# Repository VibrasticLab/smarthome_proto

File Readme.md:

# SmartHome Module

This repository contains development files for smarthome monitoring prototyping,
which intended for student final project.

Currently doesnt support any control mechanism, only measuring.

## Multi Module Version 1

### Sensors Options
- Temperature/Humidity Sensors (I2C)
    + HTU21D: [Tokped](https://www.tokopedia.com/akhishop/htu21d-temperature-and-humidity-sensor-module)
    + SHT20: [Tokped](https://www.tokopedia.com/akhishop/sht20-digital-temperature-and-humidity-sensor-module-i2c-communication)
    + SHT31-D: [Tokped](https://www.tokopedia.com/akhishop/sht31-d-temperature-humidity-sensor-module)
    + GY-213V: [Tokped](https://www.tokopedia.com/cncstorebandung/gy-213v-hdc1080-high-precision-temperature-and-humidity-sensor-module)
- Light Intensity Sensors (I2C)
    + GY302/BH1750: [Tokped](https://www.tokopedia.com/akhishop/gy-302-light-intensity-bh1750-module-sensor-intensitas-cahaya)
- CO2 Air (Analog)
    + MG-811: [Tokped](https://www.tokopedia.com/khursiot/dfrobot-analog-co2-gas-sensor-for-arduino-mg-811-sensor)
- MEMS Microphone (I2S)
    + INMP441: [Tokped](https://www.tokopedia.com/aifrobotic/inmp441-omnidirectional-microphone-module-mems-i2s-interface)

### ESP32 Pinout

NodeMCU Module: [Tokped](https://www.tokopedia.com/temins/esp32-esp-32-arduino-wifi-bluetooth-iot-development-board-micro-usb)

| I/O | Func | Connect |
|:---:|:----:|:-------:|
| EN | RESET | Pull-up Button |
| 0 | FLASH | Pull-up Button |
| 1 | TX | UART0 |
| 2 | IND | LED |
| 3 | RX | UART0 |
| 13 | SPI WS | MIC |
| 14 | SPI SCK | MIC |
| 15 | BOOT-LOG | Pull-done Resistor |
| 21 | SDA | I2C Line |
| 22 | SCL | I2C Line |
| 23 | SPI DATA | MIC |
| 33 | ADC | VBAT |
| 34 | ADC | CO2 |

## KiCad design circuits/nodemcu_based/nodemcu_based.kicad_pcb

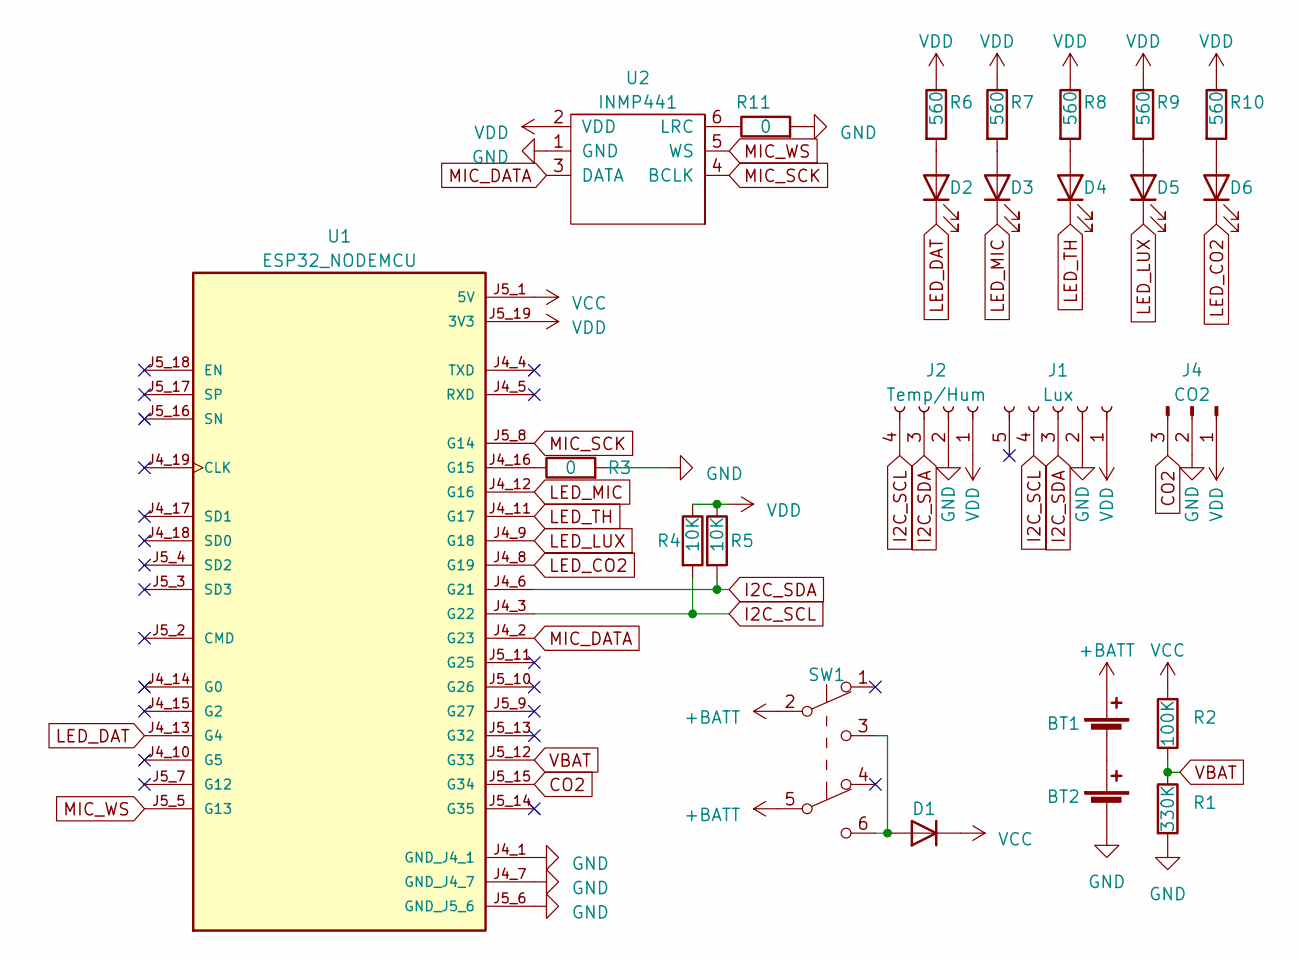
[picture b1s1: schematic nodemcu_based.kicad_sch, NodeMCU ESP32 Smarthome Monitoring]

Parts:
BT1, BT2: Battery_Cell; BatteryHolder_MPD_BH-18650-PC2
D1: D; D_DO-201_P15.24mm_Horizontal
D2, D3, D4, D5, D6: LED; LED_0805_2012Metric_Pad1.15x1.40mm_HandSolder
J1: Lux; PinSocket_1x05_P2.54mm_Vertical
J2: Temp/Hum; PinSocket_1x04_P2.54mm_Vertical
J4: CO2; PinHeader_1x03_P2.54mm_Vertical
R1: 330K; R_0805_2012Metric_Pad1.20x1.40mm_HandSolder
R2: 100K; R_0805_2012Metric_Pad1.20x1.40mm_HandSolder
R3, R11: 0; R_0805_2012Metric_Pad1.20x1.40mm_HandSolder
R4, R5: 10K; R_0805_2012Metric_Pad1.20x1.40mm_HandSolder
R6, R7, R8, R9, R10: 560; R_0805_2012Metric_Pad1.20x1.40mm_HandSolder
SW1: SW_Push_DPDT; SW_Push_2P2T_Toggle_CK_PVA2OAH5xxxxxxV2
U1: ESP32_NODEMCU; MODULE_ESP32_NODEMCU
U2: INMP441

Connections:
+BATT: BT1.1 (+), SW1.2 (B), SW1.5 (B)
CO2: J4.3, U1.J5_15 (G34)
GND: BT2.2 (-), J1.2, J2.2, J4.2, R1.2, R3.2, R11.2, U1.J4_1 (GND_J4_1), U1.J4_7 (GND_J4_7), U1.J5_6 (GND_J5_6), U2.1 (GND)
I2C_SCL: J1.4, J2.4, R4.2, U1.J4_3 (G22)
I2C_SDA: J1.3, J2.3, R5.2, U1.J4_6 (G21)
LED_CO2: D6.1 (K), U1.J4_8 (G19)
LED_DAT: D2.1 (K), U1.J4_13 (G4)
LED_LUX: D5.1 (K), U1.J4_9 (G18)
LED_MIC: D3.1 (K), U1.J4_12 (G16)
LED_TH: D4.1 (K), U1.J4_11 (G17)
MIC_DATA: U1.J4_2 (G23), U2.3 (DATA)
MIC_SCK: U1.J5_8 (G14), U2.4 (BCLK)
MIC_WS: U1.J5_5 (G13), U2.5 (WS)
unnamed: BT1.2 (-), BT2.1 (+)
unnamed: D1.2 (A), SW1.3 (C), SW1.6 (C)
unnamed: D2.2 (A), R6.2
unnamed: D3.2 (A), R7.2
unnamed: D4.2 (A), R8.2
unnamed: D5.2 (A), R9.2
unnamed: D6.2 (A), R10.2
unnamed: R3.1, U1.J4_16 (G15)
unnamed: R11.1, U2.6 (LRC)
VBAT: R1.1, R2.2, U1.J5_12 (G33)
VCC: D1.1 (K), R2.1, U1.J5_1 (5V)
VDD: J1.1, J2.1, J4.1, R4.1, R5.1, R6.1, R7.1, R8.1, R9.1, R10.1, U1.J5_19 (3V3), U2.2 (VDD)

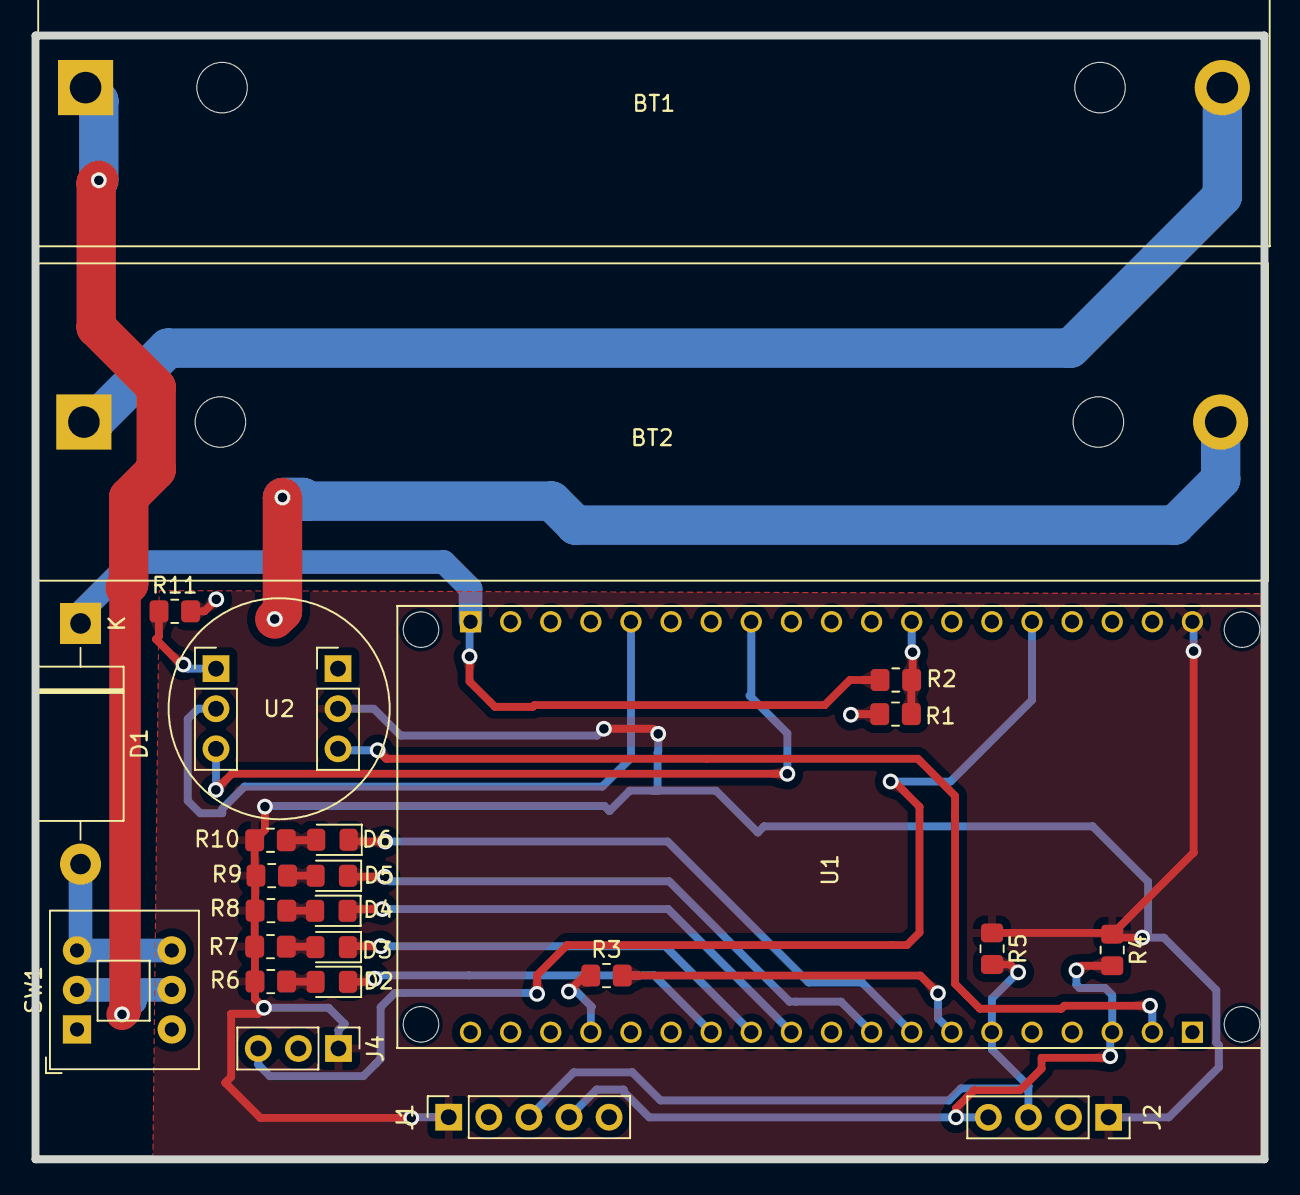
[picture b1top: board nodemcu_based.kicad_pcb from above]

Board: 2 copper layers, 77.8 x 71.2 mm, 25 parts (0 on the bottom side), 25 nets.

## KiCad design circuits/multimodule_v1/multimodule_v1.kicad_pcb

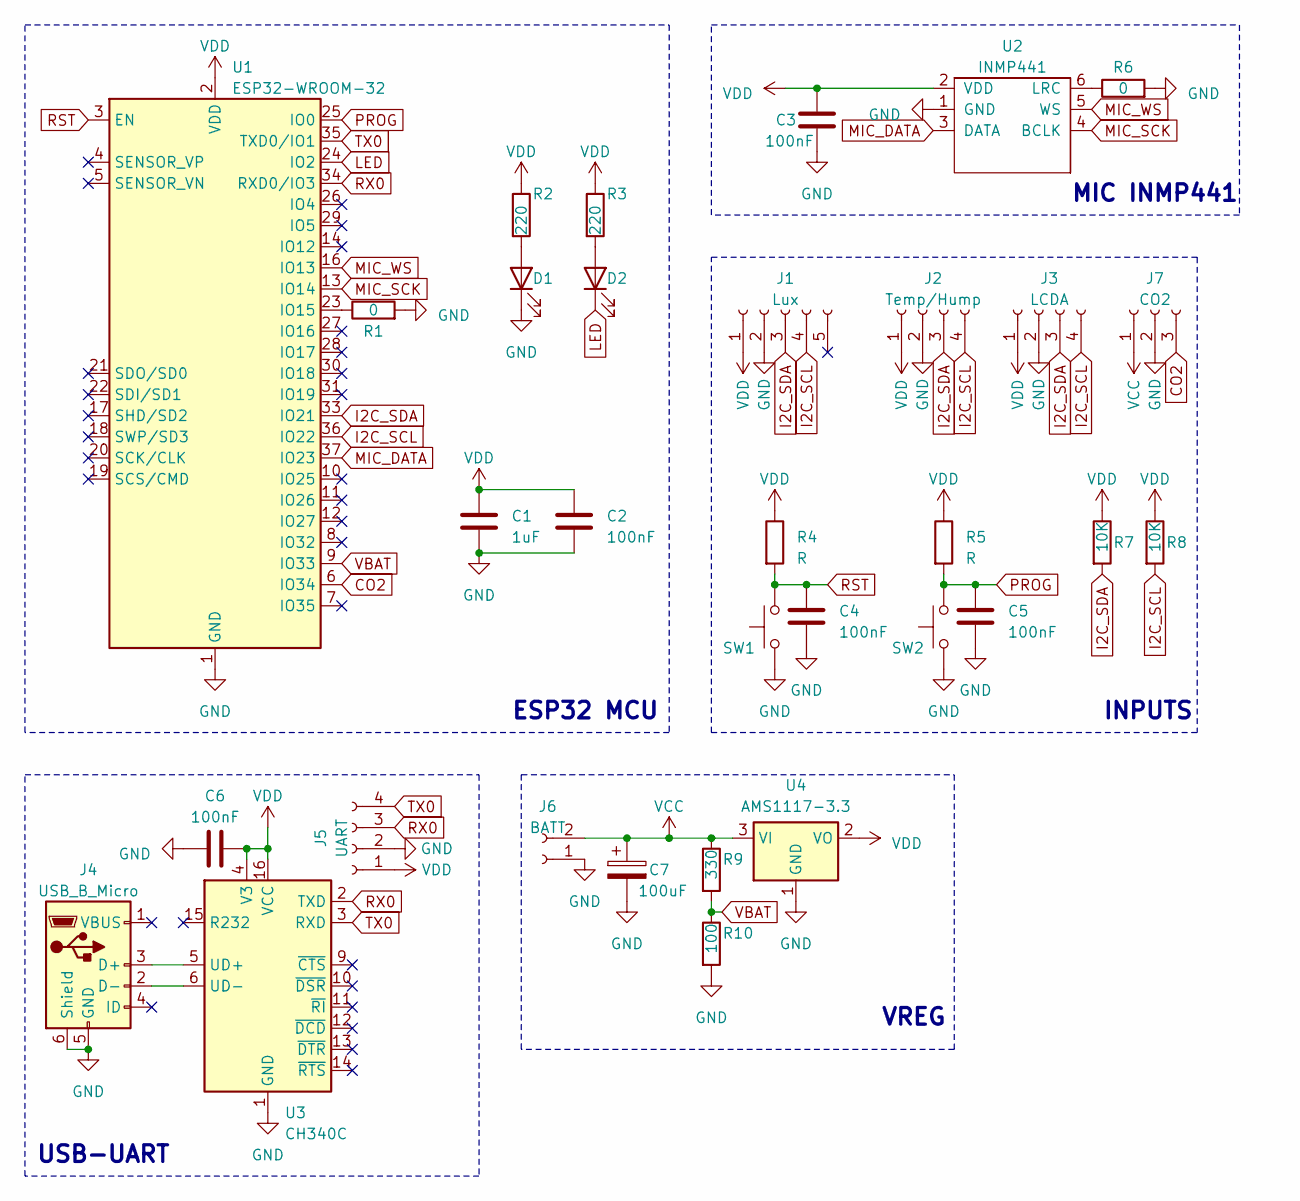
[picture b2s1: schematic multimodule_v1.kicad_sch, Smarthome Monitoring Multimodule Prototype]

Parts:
C1: 1uF; C_0805_2012Metric_Pad1.18x1.45mm_HandSolder
C2, C3, C4, C5, C6: 100nF; C_0805_2012Metric_Pad1.18x1.45mm_HandSolder
C7: 100uF; CP_Elec_4x5.8
D1, D2: LED; LED_0805_2012Metric_Pad1.15x1.40mm_HandSolder
J1: Lux; PinSocket_1x05_P2.54mm_Vertical
J2: Temp/Hump; PinSocket_1x04_P2.54mm_Vertical
J3: LCDA; PinSocket_1x04_P2.54mm_Vertical
J4: USB_B_Micro; USB_Micro-B_Wuerth_629105150521
J5: UART; PinHeader_1x04_P2.54mm_Vertical
J6: BATT; TerminalBlock_4Ucon_1x02_P3.50mm_Horizontal
J7: CO2; PinHeader_1x03_P2.54mm_Vertical
R1, R6: 0; R_0805_2012Metric_Pad1.20x1.40mm_HandSolder
R2, R3: 220; R_0805_2012Metric_Pad1.20x1.40mm_HandSolder
R4, R5: R; R_0805_2012Metric_Pad1.20x1.40mm_HandSolder
R7, R8: 10K; R_0805_2012Metric_Pad1.20x1.40mm_HandSolder
R9: 330; R_0805_2012Metric_Pad1.20x1.40mm_HandSolder
R10: 100; R_0805_2012Metric_Pad1.20x1.40mm_HandSolder
SW1, SW2: SW_Push; SW_PUSH_6mm
U1: ESP32-WROOM-32
U2: INMP441
U3: CH340C; SOIC-16_3.9x9.9mm_P1.27mm
U4: AMS1117-3.3; SOT-223-3_TabPin2

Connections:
CO2: J7.3, U1.6 (IO34)
GND: C1.2, C2.2, C3.2, C4.2, C5.2, C6.1, C7.2, D1.1 (K), J1.2, J2.2, J3.2, J4.5 (GND), J4.6 (Shield), J5.2, J6.1, J7.2, R1.2, R6.2, R10.2, SW1.1, SW2.1, U1.1 (GND), U1.15 (GND), U1.38 (GND), U1.39 (GND), U2.1 (GND), U3.1 (GND), U4.1 (GND)
I2C_SCL: J1.4, J2.4, J3.4, R8.2, U1.36 (IO22)
I2C_SDA: J1.3, J2.3, J3.3, R7.2, U1.33 (IO21)
LED: D2.1 (K), U1.24 (IO2)
MIC_DATA: U1.37 (IO23), U2.3 (DATA)
MIC_SCK: U1.13 (IO14), U2.4 (BCLK)
MIC_WS: U1.16 (IO13), U2.5 (WS)
unnamed: D1.2 (A), R2.2
unnamed: D2.2 (A), R3.2
unnamed: J4.3 (D+), U3.5 (UD+)
unnamed: J4.2 (D-), U3.6 (UD-)
unnamed: R1.1, U1.23 (IO15)
unnamed: R6.1, U2.6 (LRC)
PROG: C5.1, R5.2, SW2.2, U1.25 (IO0)
RST: C4.1, R4.2, SW1.2, U1.3 (EN)
RX0: J5.3, U1.34 (RXD0/IO3), U3.2 (TXD)
TX0: J5.4, U1.35 (TXD0/IO1), U3.3 (RXD)
VBAT: R9.2, R10.1, U1.9 (IO33)
VCC: C7.1, J6.2, J7.1, R9.1, U4.3 (VI)
VDD: C1.1, C2.1, C3.1, C6.2, J1.1, J2.1, J3.1, J5.1, R2.1, R3.1, R4.1, R5.1, R7.1, R8.1, U1.2 (VDD), U2.2 (VDD), U3.4 (V3), U3.16 (VCC), U4.2 (VO)

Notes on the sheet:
USB-UART
ESP32 MCU
VREG
INPUTS
MIC INMP441

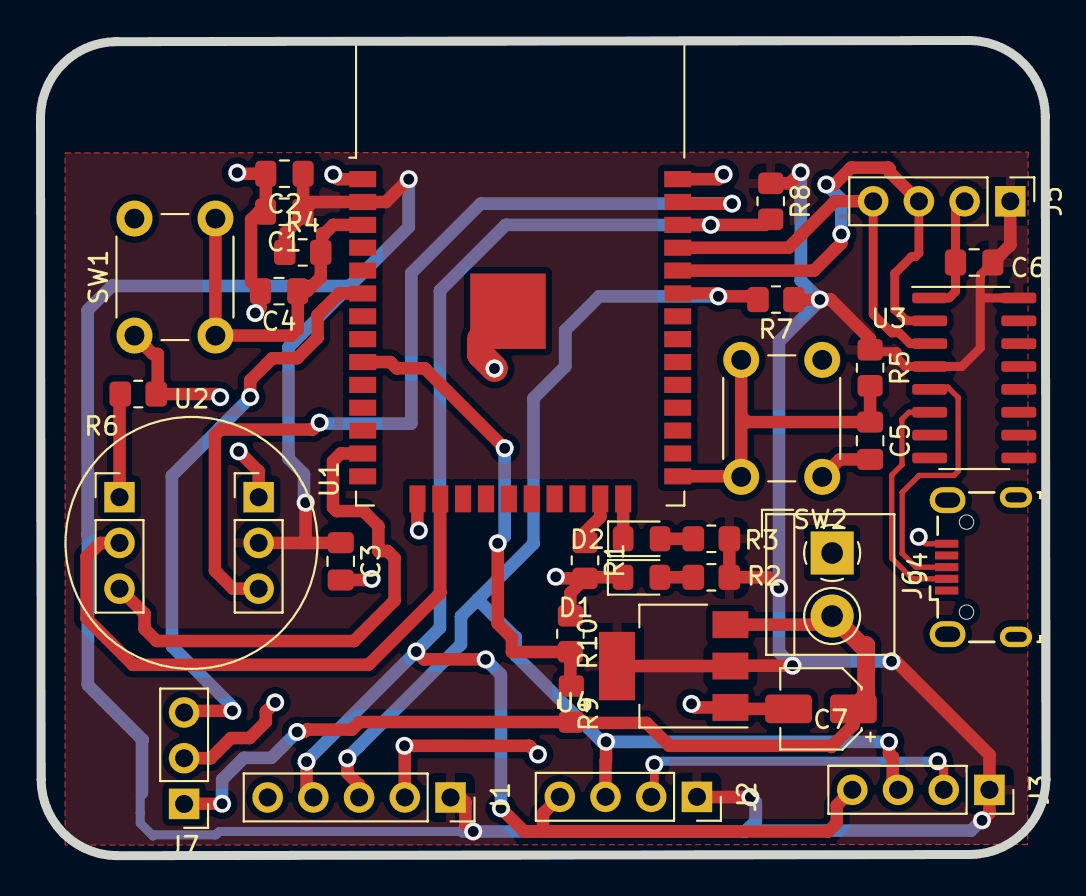
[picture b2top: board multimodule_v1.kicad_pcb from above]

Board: 2 copper layers, 55.9 x 45.3 mm, 32 parts (0 on the bottom side), 21 nets.

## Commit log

2023-03-31 initial development
2023-03-31 Create MIT License
2023-04-01 Initial Schematic
2023-04-01 Initial Footprint
2023-04-01 Update Custom module
2023-04-01 NodeMCU ESP32 Based
2023-04-01 NOdeMCU Smarthome
2023-04-01 Tinggal Latex/PDF nya
2023-04-02 Small PCB version
2023-04-02 Nyicil Dokumen
2023-04-02 Dokumen Usulan
2023-04-02 Doc Usulan
2023-04-03 Document Usulan
